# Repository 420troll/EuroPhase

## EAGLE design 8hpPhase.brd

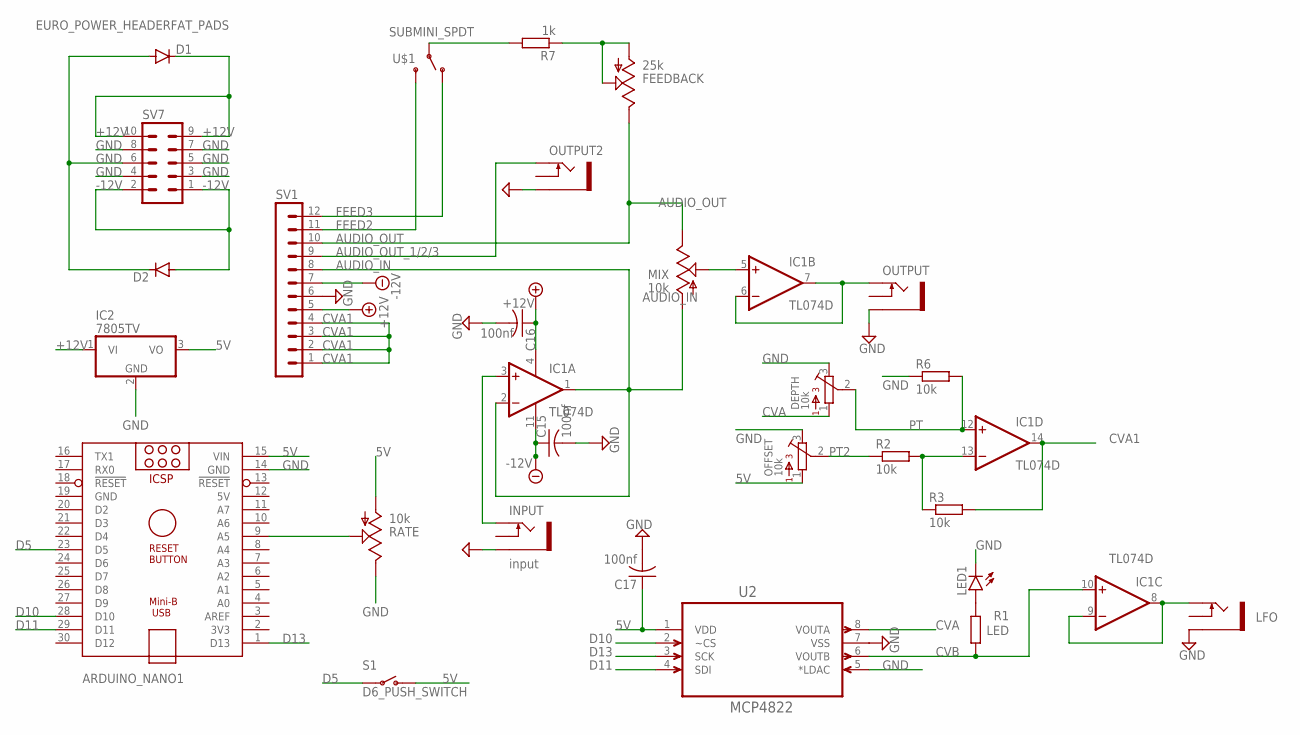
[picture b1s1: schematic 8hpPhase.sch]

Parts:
ARDUINO_NANO1: ARDUINO_NANO
C15, C16, C17: 100nf; C0805
D1, D2: DIODE-SOD106A-R; SOD106A-R
DEPTH: 10k; BOURNS_3362P_TRIMMER
FEEDBACK: 25k; 9MM_SNAP-IN_POT
IC1: TL074D; SO14
IC2: 7805TV; TO220V
INPUT: input; WQP-PJ301M-12_JACK
LED1: LED3MM
LFO: output; WQP-PJ301M-12_JACK
MIX: 10k; 9MM_SNAP-IN_POT
OFFSET: 10k; BOURNS_3362P_TRIMMER
OUTPUT, OUTPUT2: output; WQP-PJ301M-12_JACK
R1: LED; M0805
R2, R3, R6: 10k; M0805
R7: 1k; M0805
RATE: 10k; 9MM_SNAP-IN_POT
S1: D6_PUSH_SWITCH
SV1: MA12-1
SV7: EURO_POWER_HEADERFAT_PADS; EURO_PWR_HEADER_FAT
U2: MCP4822; SOIC127P600X175-8N
U$1: SUBMINI_SPDT; SUBMINI_TOGGLE

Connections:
5V: ARDUINO_NANO1.12 (5V), ARDUINO_NANO1.15 (VIN), C17.1, IC2.3 (VO), OFFSET.1, RATE.1 (A), S1.P$1 (O), S1.P$2 (O), U2.1 (VDD)
+12V: C16.1, D1.C, IC1.4 (V+), IC2.1 (VI), SV1.5, SV7.9, SV7.10
-12V: C15.1, D2.A, IC1.11 (V-), SV1.7, SV7.1, SV7.2
AUDIO_IN: IC1.1 (OUT), IC1.2 (-IN), MIX.1 (A), SV1.8
AUDIO_OUT: FEEDBACK.3 (E), MIX.3 (E), SV1.10
AUDIO_OUT_1/2/3: OUTPUT2.P$1_TIP (TIP), SV1.9
CVA: DEPTH.1, U2.8 (VOUTA)
CVA1: IC1.14 (OUT), R3.2, SV1.1, SV1.2, SV1.3, SV1.4
CVB: IC1.10 (+IN), R1.1, U2.6 (VOUTB)
D5: ARDUINO_NANO1.23 (D5), S1.P$3, S1.P$4
D10: ARDUINO_NANO1.28 (D10), U2.2 (~CS)
D11: ARDUINO_NANO1.29 (D11), U2.4 (SDI)
D13: ARDUINO_NANO1.1 (D13), U2.3 (SCK)
FEED2: SV1.11, U$1.3 (S)
FEED3: SV1.12, U$1.1 (O)
GND: ARDUINO_NANO1.14 (GND), ARDUINO_NANO1.19 (GND), C15.2, C16.2, C17.2, D1.A, D2.C, DEPTH.3, IC2.2 (GND), INPUT.P$3_SLEEVE (SLEEVE), LED1.K (C), LFO.P$3_SLEEVE (SLEEVE), OFFSET.3, OUTPUT.P$3_SLEEVE (SLEEVE), OUTPUT2.P$3_SLEEVE (SLEEVE), R6.1, RATE.3 (E), SV1.6, SV7.3, SV7.4, SV7.5, SV7.6, SV7.7, SV7.8, U2.5 (*LDAC), U2.7 (VSS)
unnamed: IC1.13 (-IN), R2.2, R3.1
unnamed: IC1.8 (OUT), IC1.9 (-IN), LFO.P$1_TIP (TIP)
unnamed: LED1.A, R1.2
unnamed: ARDUINO_NANO1.9 (A5), RATE.2 (S)
unnamed: IC1.5 (+IN), MIX.2 (S)
unnamed: IC1.6 (-IN), IC1.7 (OUT), OUTPUT.P$1_TIP (TIP)
unnamed: IC1.3 (+IN), INPUT.P$1_TIP (TIP)
unnamed: R7.2, U$1.COM (COMMON)
unnamed: FEEDBACK.1 (A), FEEDBACK.2 (S), R7.1
PT: DEPTH.2, IC1.12 (+IN), R6.2
PT2: OFFSET.2, R2.1

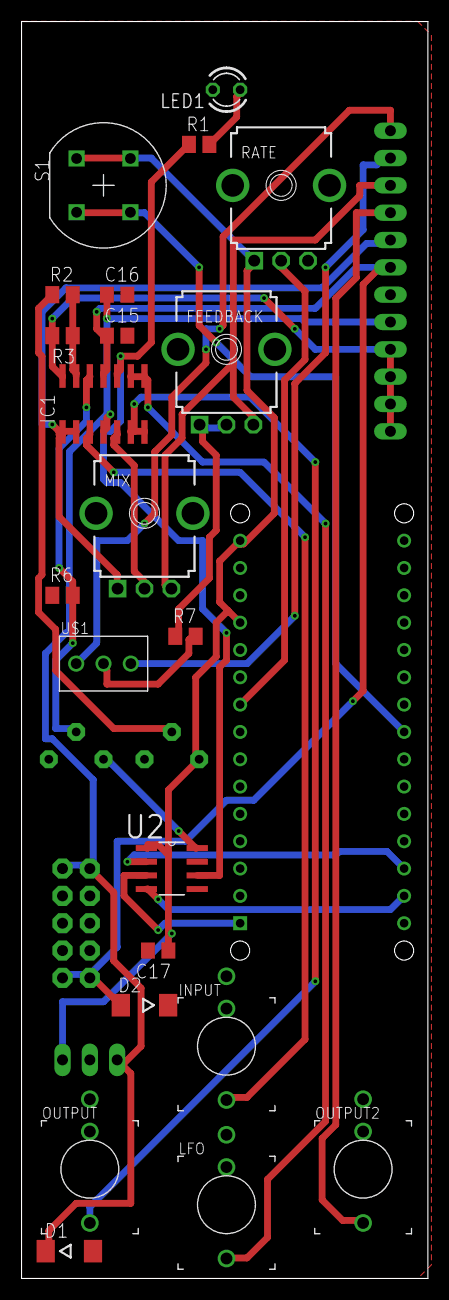
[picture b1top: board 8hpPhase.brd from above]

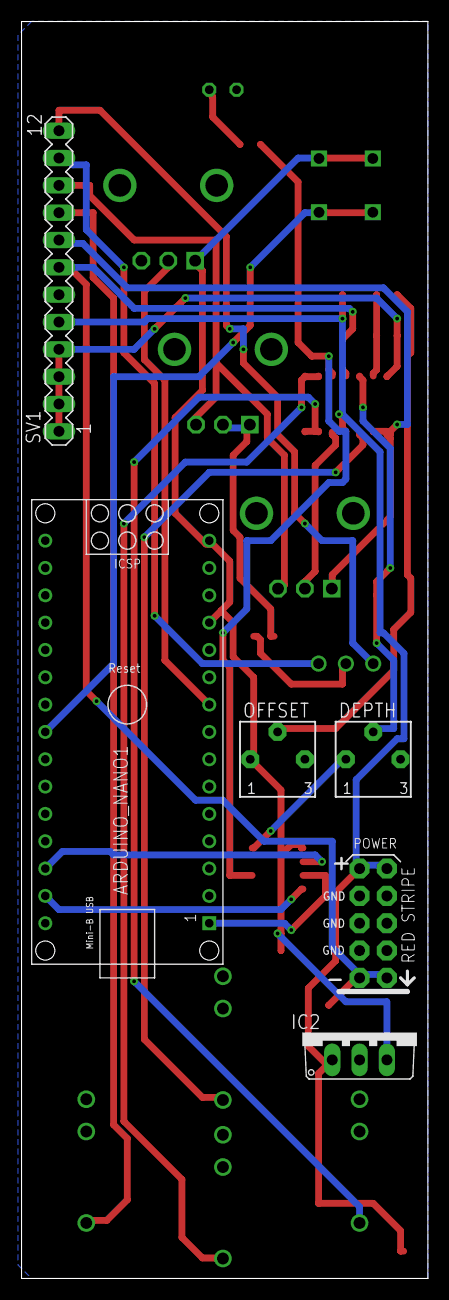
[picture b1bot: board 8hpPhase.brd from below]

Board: 2 copper layers, 37.8 x 116.8 mm, 28 parts (6 on the bottom side), 27 nets.
